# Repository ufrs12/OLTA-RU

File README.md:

# OLTA

## Open Logical Tools Architecture  
  
Архитектрура стека [OLxA](https://github.com/ufrs12/OLxA), описывающая разработку, производство, внедрение, эксплуатацию средств автоматизации архитектур [OLIA](https://github.com/ufrs12/OLIA-RU) и OLHA.

### PCB

[OLTA PCB](https://github.com/ufrs12/OLTA-RU/tree/main/PCB) - раздел, описывающий разработку, прототипирование и производство печатных плат. Описывает средства и технологии используемые в этих целях.

### LAB
OLTA LAB - раздел, описывающий средства и технологии испоьзуемые для измерений, экспериментов, тестирования.

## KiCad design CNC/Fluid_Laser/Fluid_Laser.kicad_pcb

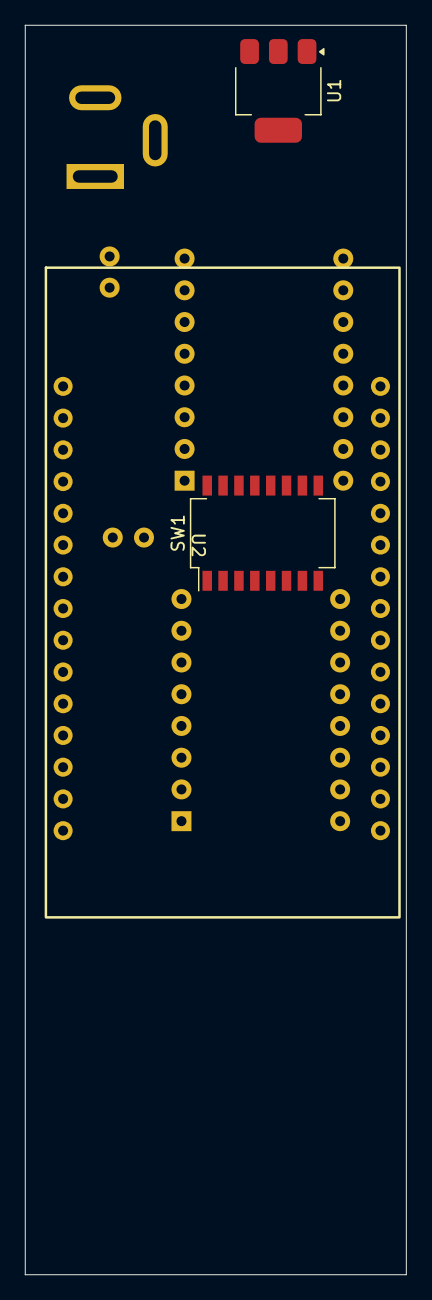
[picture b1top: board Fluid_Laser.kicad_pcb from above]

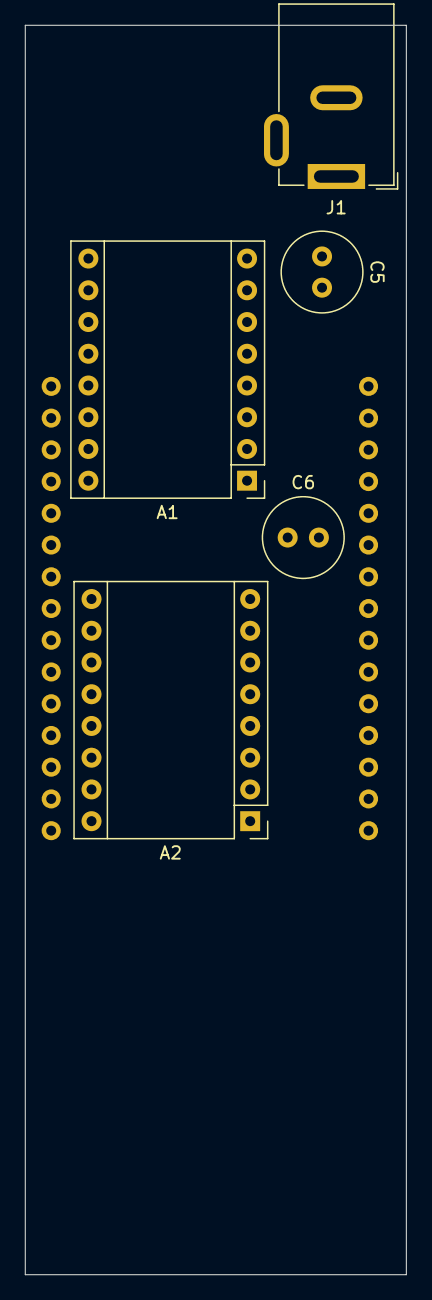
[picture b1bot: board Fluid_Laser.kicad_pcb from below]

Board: 2 copper layers, 30.5 x 100.0 mm, 8 parts (5 on the bottom side), 8 nets, no tracks yet.

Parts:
A1, A2: A4988; Pololu_Breakout-16_15.2x20.3mm
C5, C6: 100uF; C_Radial_D6.3mm_H11.0mm_P2.50mm
J1: Barrel_Jack; BarrelJack_GCT_DCJ200-10-A_Horizontal
SW1: SW_DIP_x08; SW_DIP_SPSTx08_Slide_Copal_CHS-08B_W7.62mm_P1.27mm
U1: AMS1117-5.0; SOT-223-3_TabPin2
U2: ESP32S_30pin

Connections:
+3.3V: A1.2 (VDD), A2.2 (VDD), U2.16 (3.3v)
+5V: U1.2 (VO), U2.1 (VIN)
+VDC: A1.8 (VMOT), A2.8 (VMOT), C5.1, C6.1, J1.1, U1.3 (VI)
GND: A1.1 (GND), A1.7 (GND), A2.1 (GND), A2.7 (GND), C5.2, C6.2, J1.2, U1.1 (GND), U2.2 (GND), U2.17 (GND)
X_Dir: A1.15 (STEP), U2.4 (GPIO12)
X_Step: A1.16 (DIR), U2.5 (GPIO14)
Y_Dir: A2.16 (DIR), U2.8 (GPIO25)
Y_Step: A2.15 (STEP), U2.7 (GPIO26)

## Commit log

2024-04-01 Update LICENSE
